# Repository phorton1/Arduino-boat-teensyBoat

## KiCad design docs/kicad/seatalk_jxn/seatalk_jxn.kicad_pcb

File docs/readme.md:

# teensyBoat.ino

**Home** --
**[Electronics](electronics.md)** --
**[3DP](3dp.md)** --
**[Commands](commands.md)**

repos: **[phorton1](https://github.com/phorton1)** --
**teensyBoat Firmware** --
**[teensyBoat App](https://github.com/phorton1/base-apps-teensyBoat/blob/master/docs/readme.md)** --
**[Boat Library](https://github.com/phorton1/Arduino-libraries-Boat/blob/master/docs/readme.md)** --
**[tbESP32 WiFi](https://github.com/phorton1/Arduino-boat-tbESP32/blob/master/docs/readme.md)** --
**[teensyWind Tester](https://github.com/phorton1/Arduino-boat-teensyWind/blob/master/docs/readme.md)** --
**[teensyGPS](https://github.com/phorton1/Arduino-boat-teensyGPS/blob/master/docs/readme.md)**

**teensyBoat.ino** is a Teensy 4.0 firmware and custom PCB that bridges three marine
instrument protocols -- **Seatalk1**, **NMEA 0183**, and **NMEA 2000** -- on a single
compact board.  It is the primary hardware in a three-repo marine electronics system
and the natural entry point for anyone exploring, building, or extending it.  The
firmware includes a complete **virtual boat simulator** and nine **virtual instrument
simulators** that can drive any combination of the three protocols, making it a
self-contained desktop test harness for Raymarine chartplotters and other marine
electronics.  A companion **GP8 connector** on the board drives the analog and pulse
inputs of Raymarine ST50 instruments directly, enabling bench testing of ST50 Speed,
Wind, and Depth instruments without a real boat or real transducers.

## The Three-Repo System

teensyBoat.ino is the hardware hub at the center of a tightly coupled three-repo system:

- **[Arduino-boat-teensyBoat](https://github.com/phorton1/Arduino-boat-teensyBoat)**
  (this repo) -- the Teensy 4.0 firmware and PCB.  Runs standalone as a protocol
  bridge and simulator; exposes a USB serial command interface for monitoring and control.

- **[base-apps-teensyBoat](https://github.com/phorton1/base-apps-teensyBoat)** --
  the companion wxPerl Windows desktop application.  Connects to the firmware over USB
  serial or UDP (via tbESP32) and provides real-time display of boat simulator state,
  live protocol monitoring, and virtual instrument configuration.

- **[Arduino-libraries-Boat](https://github.com/phorton1/Arduino-libraries-Boat)** --
  the shared C++ Arduino library included by the firmware.  Implements the virtual boat
  and instrument simulators, all three protocol stacks, the binary packet framing layer,
  and defines the packet type constants shared with the wxPerl application.

The three repos have independent git histories but are tightly coupled at the
protocol level.  The binary packet type constants defined in the Boat library must
match those in the wxPerl application's `tbBinary.pm`; they are kept in sync manually.

## Binary Serial Protocol

The firmware and wxPerl application communicate over a **binary packet protocol**
carried on the same USB serial port as text output -- or forwarded over UDP by the
**[tbESP32](https://github.com/phorton1/Arduino-boat-tbESP32)** WiFi bridge.
Both the text command interface and the binary telemetry stream are active simultaneously
on a single connection.

Every binary packet begins with a **0x02** start byte (BINARY_FLAG), followed by a
16-bit little-endian payload length and a 16-bit little-endian type code.  Multiple
streams can be active at once; the wxPerl application enables each stream it needs on
connect and disables them on close.

| Packet type         | Value  | Content                                              |
| ------------------- | ------ | ---------------------------------------------------- |
| BINARY_TYPE_PROG    | 0x0001 | Virtual instrument port-mask config and monitor flags |
| BINARY_TYPE_SIM     | 0x0002 | Full boat simulator state (50+ fields, at 1 Hz while running) |
| BINARY_TYPE_ST1     | 0x0010 | Decoded Seatalk1 datagrams from port ST1             |
| BINARY_TYPE_ST2     | 0x0020 | Decoded Seatalk1 datagrams from port ST2             |
| BINARY_TYPE_0183A   | 0x0100 | Raw NMEA 0183 sentences from port A                  |
| BINARY_TYPE_0183B   | 0x0200 | Raw NMEA 0183 sentences from port B                  |
| BINARY_TYPE_2000    | 0x1000 | Decoded NMEA 2000 PGN data                           |

The framing layer is implemented in `boatBinary.cpp` (`startBinary()` / `endBinary()`
in the Boat library) and consumed by the wxPerl application's binary receive loop.

## Hardware

The custom PCB and 3D-printed enclosure design files are included in this repository.

- **[Electronics](electronics.md)** -- KiCad schematics and PCB layouts for the current
  and previous board revisions, Gerber files, and CNC milling gcode for the home-milled
  board1 revision.

- **[3DP](3dp.md)** -- STL and 3MF files for the 3D-printed enclosure, and pre-sliced
  PETG printer gcode.

## Command Interface

The firmware accepts a comprehensive set of **text commands** -- plain
ASCII, case-insensitive, `KEY=VALUE` or `VERB` form, newline-terminated
-- on its USB serial port.  The same commands are forwarded by the
companion **tbESP32** WiFi bridge and by the **teensyBoat.pm** wxPerl
application's HTTP `/api/command` endpoint.

See **[Commands](commands.md)** for the complete reference: virtual boat
control, instrument configuration, protocol monitoring, GP8/ST50 testing,
NMEA 2000 device queries, and binary streaming control.

## Credits

- [**Paul Stoffregen**](https://www.pjrc.com/teensy/) --
  Creator of the Teensy microcontroller platform.  teensyBoat.ino is built
  for the Teensy 4.0.

- [**Thomas Knauf**](http://www.thomasknauf.de/seatalk.htm) --
  *SeaTalk Technical Reference Revision 3.23*.  The primary public reference for
  the Seatalk1 datagram protocol.  The
  **[Arduino Boat Library](https://github.com/phorton1/Arduino-libraries-Boat/blob/master/docs/readme.md)**
  used by this firmware builds on, extends, and in places corrects that work.
  Corrections, extensions, and new datagrams not in Knauf are catalogued on the
  **[Seatalk Knowledge](https://github.com/phorton1/Arduino-libraries-Boat/blob/master/docs/new_st_knowledge.md)**
  page in the Boat Library documentation.

## License

This software is released under the
[**GNU General Public License v3**](../LICENSE.TXT).

## Please Also See

- [**phorton1/base-apps-teensyBoat**](https://github.com/phorton1/base-apps-teensyBoat) --
  The companion wxPerl Windows application.  Monitors and controls the teensyBoat
  firmware over USB serial or WiFi; provides real-time display of simulator state,
  protocol monitoring, and virtual instrument configuration.

- [**phorton1/Arduino-libraries-Boat**](https://github.com/phorton1/Arduino-libraries-Boat) --
  The shared C++ library used by this firmware.  Implements the virtual boat and
  instrument simulators, all three protocol encoders and decoders, and the binary
  packet protocol shared with the wxPerl application.

- [**phorton1/Arduino-boat-teensyGPS**](https://github.com/phorton1/Arduino-boat-teensyGPS) --
  A related device built on the same Boat library: a Teensy/Neo6M GPS that outputs
  Seatalk1 and/or NMEA 2000 for integration into an existing marine instrument network.

- [**phorton1/Arduino-boat-tbESP32**](https://github.com/phorton1/Arduino-boat-tbESP32) --
  The ESP32 WiFi bridge that plugs into teensyBoat's GP8 connector, forwarding the
  USB serial binary protocol over UDP to the wxPerl application over a local network.

- [**phorton1/Arduino-boat-teensyWind**](https://github.com/phorton1/Arduino-boat-teensyWind) --
  A companion device that interfaces directly with a Raymarine ST50/ST60 wind vane
  transducer and outputs Seatalk1 or NMEA 2000.

- [**phorton1/base-apps-raymarine**](https://github.com/phorton1/base-apps-raymarine) --
  Documentation of the reverse-engineered Raymarine SeatalkHS ethernet protocol
  suite.  The teensyBoat hardware was the active instrument platform during that work.

---

**Next:** [Electronics](electronics.md)

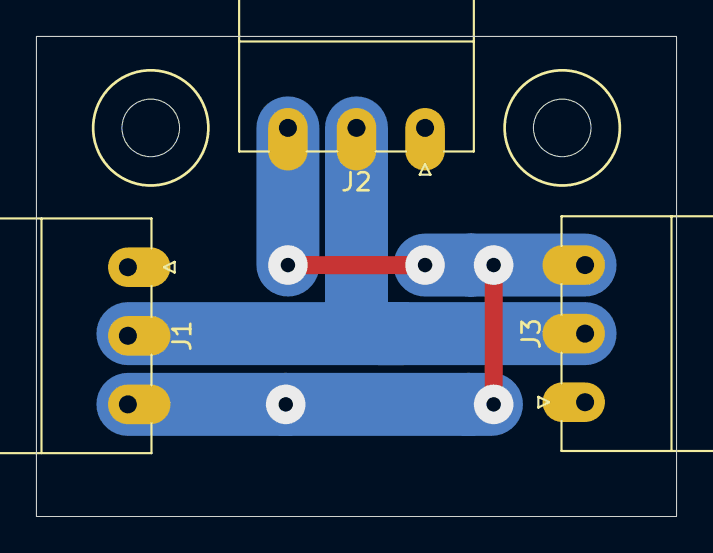
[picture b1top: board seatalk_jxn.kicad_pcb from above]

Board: 2 copper layers, 35.6 x 26.7 mm, 3 parts (0 on the bottom side), 3 nets.

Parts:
J1, J2, J3: Conn_01x03; myPheonix3x3.81_right

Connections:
+12V: J1.2, J2.2, J3.2
DATA: J1.3, J2.3, J3.3
GND: J1.1, J2.1, J3.1

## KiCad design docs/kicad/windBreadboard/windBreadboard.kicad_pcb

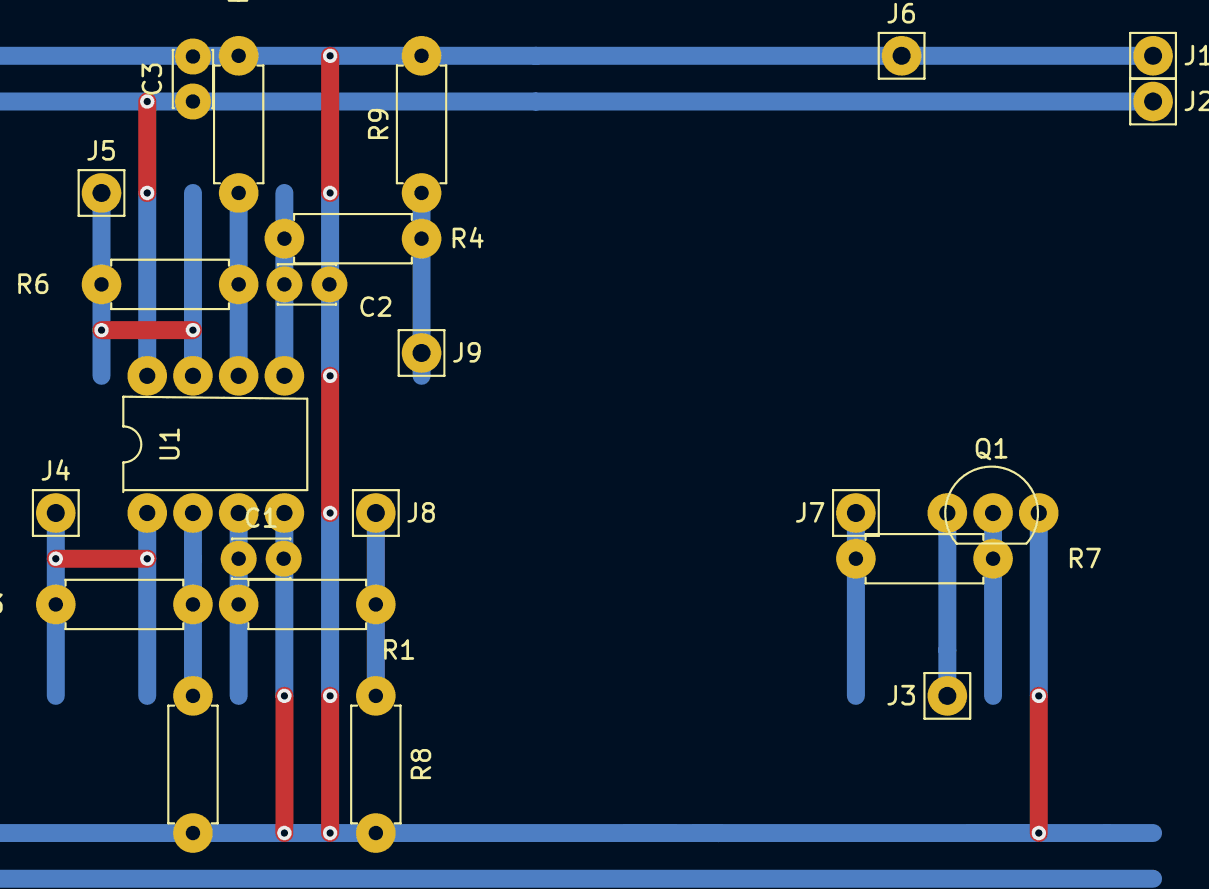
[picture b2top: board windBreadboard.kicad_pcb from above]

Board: 2 copper layers, 23 parts (0 on the bottom side), 13 nets.

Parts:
C1, C2, C3: 100nf; myCapCeramicSmall
J1: ST_GND; myPinHeader_1x01
J2: ST_12V; myPinHeader_1x01
J3: WIND_PULSE_YELLOW; myPinHeader_1x01
J4: SIGNALA_GREEN; myPinHeader_1x01
J5: SIGNALB_BLUE; myPinHeader_1x01
J6: GP8_GND; myPinHeader_1x01
J7: GP8_PULSE_YELLOW; myPinHeader_1x01
J8: GP8_PWMA_GREEN; myPinHeader_1x01
J9: GP8_PWMB_BLUE; myPinHeader_1x01
Q1: BC546; myTransistor
R1, R2, R4, R5, R8, R9: 10K; myResistor
R3, R6: 22K; myResistor
R7: 1K; myResistor
U1: LM358; myDip8

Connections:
+12V: C3.1, J2.1, U1.8
GND: C1.2, C2.2, C3.2, J1.1, J6.1, Q1.3, R2.2, R5.2, R8.2, R9.2, U1.4
unnamed: C1.1, R1.1, U1.3
unnamed: C2.1, R4.1, U1.5
unnamed: Q1.2, R7.1
unnamed: R2.1, R3.2, U1.2
unnamed: R5.1, R6.2, U1.6
PWMA_GREEN: J8.1, R1.2, R8.1
PWMB_BLUE: J9.1, R4.2, R9.1
SIGNALA_GREEN: J4.1, R3.1, U1.1
SIGNALB_BLUE: J5.1, R6.1, U1.7
SPEED_PULSE_YELLOW: J7.1, R7.2
WIND_PULSE_YELLOW: J3.1, Q1.1

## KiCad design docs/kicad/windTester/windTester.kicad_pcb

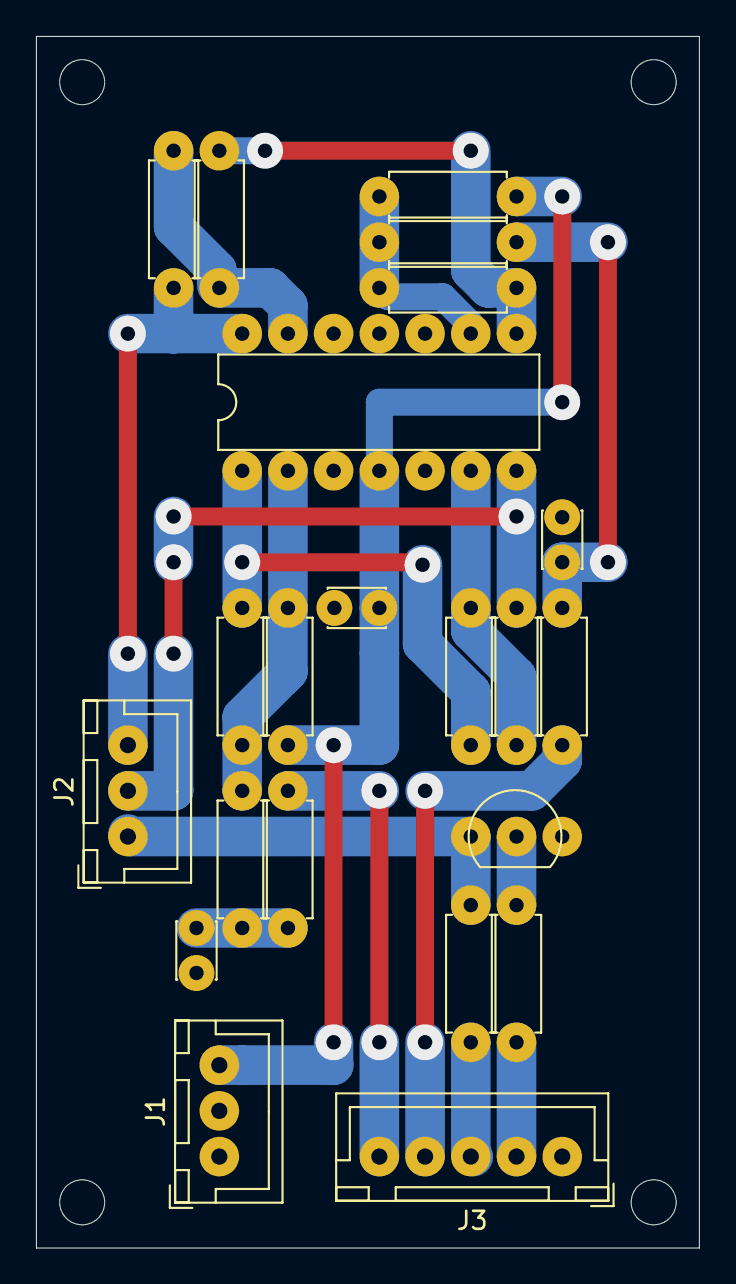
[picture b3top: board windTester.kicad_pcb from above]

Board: 2 copper layers, 36.8 x 67.3 mm, 22 parts (0 on the bottom side), 18 nets.

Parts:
C1, C2, C3: 100nf; myCapCeramicSmall
J1: SEATALK; myJSTx03
J2: INSTRUMENT; myJSTx03
J3: TEENSY_PCB; myJSTx05
Q1: BC547; myTransistor
R1, R2, R5, R6, R7, R8, R11, R12, R14: 10K; myResistor
R3, R9: 68K; myResistor
R4, R10: 12K; myResistor
R13: 1K; myResistor
U1: LM324A; myDip14

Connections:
+5V: J3.3, R14.2
+12V: C3.1, J1.3, R3.1, R9.1, U1.4
GND: C1.2, C2.2, C3.2, J1.1, J3.1, Q1.3, U1.3, U1.5, U1.10, U1.11, U1.12
unnamed: C1.1, R1.1, R2.2
unnamed: C2.1, R7.1, R8.2
unnamed: Q1.2, R13.1
unnamed: R2.1, R3.2, R4.2, U1.2
unnamed: R4.1, R5.2, U1.1
unnamed: R5.1, R6.2, U1.6
unnamed: R10.1, R11.2, U1.8
unnamed: R8.1, R9.2, R10.2, U1.9
unnamed: R11.1, R12.2, U1.13
PWMA: J3.5, R1.2
PWMB: J3.4, R7.2
SIGNALA: J2.2, R6.1, U1.7
SIGNALB: J2.3, R12.1, U1.14
SPEED_SQUARE: J3.2, R13.2
WIND_SQUARE: J2.1, Q1.1, R14.1

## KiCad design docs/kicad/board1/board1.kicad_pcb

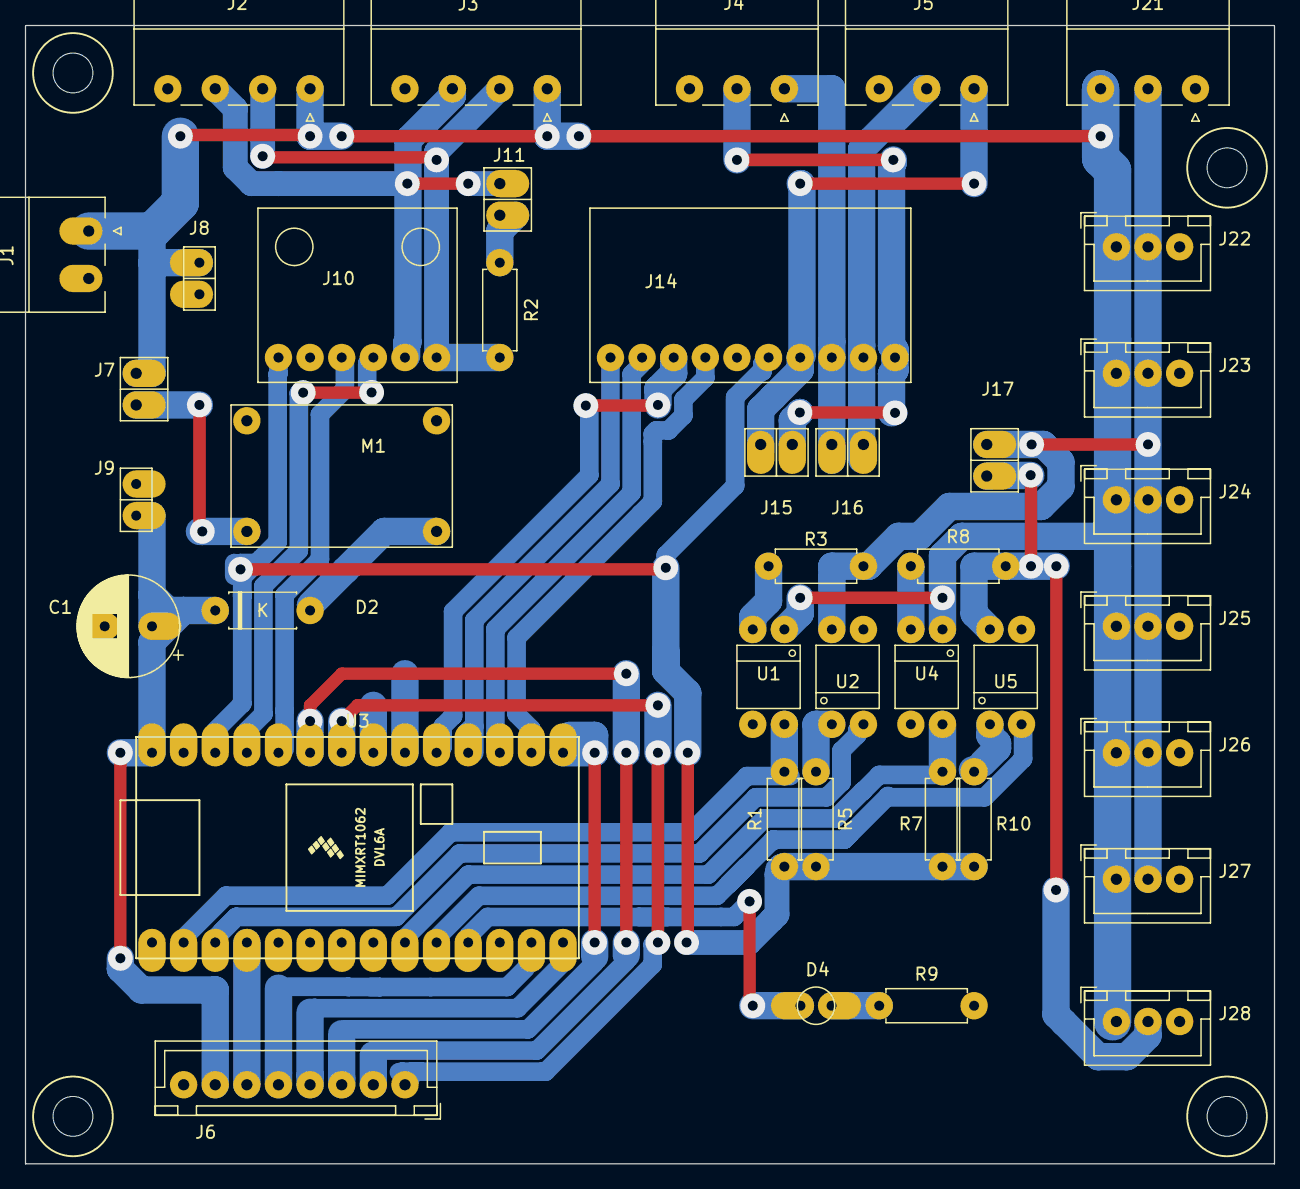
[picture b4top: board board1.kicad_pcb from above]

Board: 2 copper layers, 100.3 x 91.4 mm, 40 parts (0 on the bottom side), 37 nets.

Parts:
C1: 100uf; CP_my100uf
D2: 1N5819; myDiodeSchotsky
D4: ALIVE_LED; led_small_red
J1: INST_POWER; myPheonix2x3.81_right
J2, J3: NMEA2000; myPheonix4x3.81_right
J4: 83A; myPheonix3x3.81_right
J5: 83B; myPheonix3x3.81_right
J6: TEST_RIG; myJSTx08
J7: BUCK_PWR; pinHeader1x2
J8: 12V_TEST; pinSocket1x2
J9: 5V_TEST; pinSocket1x2
J10: SN65HVD230; CANBUS_Module1
J11: CAN_TERMINATOR; pinHeader1x2
J14: MAX3232; MAX3232_Module
J15: AIS; pinHeader1x2
J16: GPS; pinHeader1x2
J17: ST_CONNECTED; pinHeader1x2
J21: ST1; myPheonix3x3.81_right
J22, J23, J24, J25, J26, J27: ST1; myJSTx03
J28: ST2; myJSTx03
M1: BUCK01; myMini360BuckConverter
R1: 10K; myResistor
R2: 120; myResistor
R3, R8: 4.7K; myResistor
R5, R9, R10: 220; myResistor
R7: 10k; myResistor
U1, U2, U4, U5: TLP521; myDip4
U3: myTeensy4.0; teensy40

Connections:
83A_IN: J4.2, J14.10, J15.2
83A_OUT: J4.1, J14.8, J16.1
83B_IN: J5.2, J14.9, J16.2
83B_OUT: J5.1, J14.7, J15.1
+3V3: J10.1, J14.6, R1.1, R5.2, R7.1, R10.2, U3.26
+5V: C1.1, D2.1, J6.7, J9.1, U3.28
+12V: J1.1, J2.1, J3.1, J7.2, J8.1, J21.3, J22.1, J23.1, J24.1, J25.1, J26.1, J27.1, J28.1, U1.1, U4.1
ALIVE_LED: D4.2, U3.11
CANH: J2.3, J3.3, J10.5, J11.2
CANL: J2.2, J3.2, J10.6, R2.1
CRX: J10.3, U3.24
CTX: J10.4, U3.25
GND: C1.2, J1.2, J2.4, J3.4, J4.3, J5.3, J6.8, J8.2, J9.2, J10.2, J14.5, J21.1, J22.3, J23.3, J24.3, J25.3, J26.3, J27.3, J28.3, M1.1, M1.2, R9.2, U1.3, U2.3, U3.1, U3.27, U4.3, U5.3
MISO-UDP_ENABLE: J6.4, U3.14
MOSI-GP: J6.5, U3.13
unnamed: D2.2, M1.3
unnamed: D4.1, R9.1
unnamed: J7.1, M1.4
unnamed: J11.1, R2.2
unnamed: R3.1, U1.2
unnamed: R5.1, U2.1
unnamed: R8.1, U4.2
unnamed: R10.1, U5.1
RX1: R1.2, U1.4, U3.2
RX2: R7.2, U3.9, U4.4
RX3: J14.2, U3.17
RX4: J14.1, U3.18
RX5-T_CS: J6.2, U3.23
SCLK-GP: J6.3, U3.15
SPEED_PULSE-LCD_CS: J6.6, U3.4
ST1: J17.2, J21.2, J22.2, J23.2, J24.2, J25.2, J26.2, J27.2, R3.2, U2.4
ST2: J17.1, J28.2, R8.2, U5.4
TX1: U2.2, U3.3
TX2: U3.10, U5.2
TX3: J14.4, U3.16
TX4: J14.3, U3.19
TX5-LCD_DC: J6.1, U3.22

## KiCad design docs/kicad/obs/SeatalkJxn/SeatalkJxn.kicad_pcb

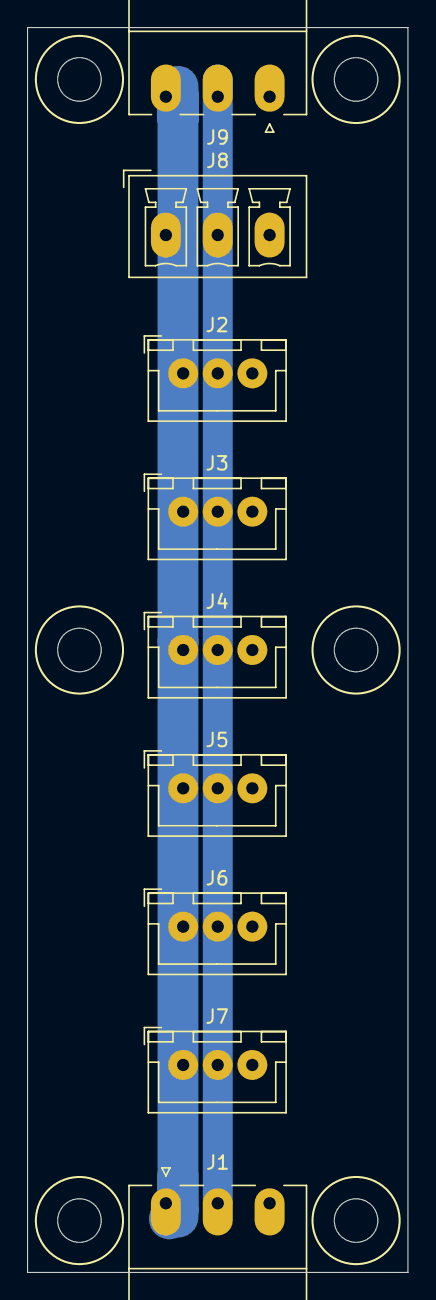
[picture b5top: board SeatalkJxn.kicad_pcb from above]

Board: 2 copper layers, 27.9 x 91.4 mm, 9 parts (0 on the bottom side), 3 nets.

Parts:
J1, J9: Conn_01x03; myPheonix3x3.81_right
J2, J3, J4, J5, J6, J7: Conn_01x03; myJSTx03
J8: Conn_01x03; myPhoenix3x3.81_vertical

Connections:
+12V: J1.1, J2.1, J3.1, J4.1, J5.1, J6.1, J7.1, J8.1, J9.3
GND: J1.3, J2.3, J3.3, J4.3, J5.3, J6.3, J7.3, J8.3, J9.1
data: J1.2, J2.2, J3.2, J4.2, J5.2, J6.2, J7.2, J8.2, J9.2

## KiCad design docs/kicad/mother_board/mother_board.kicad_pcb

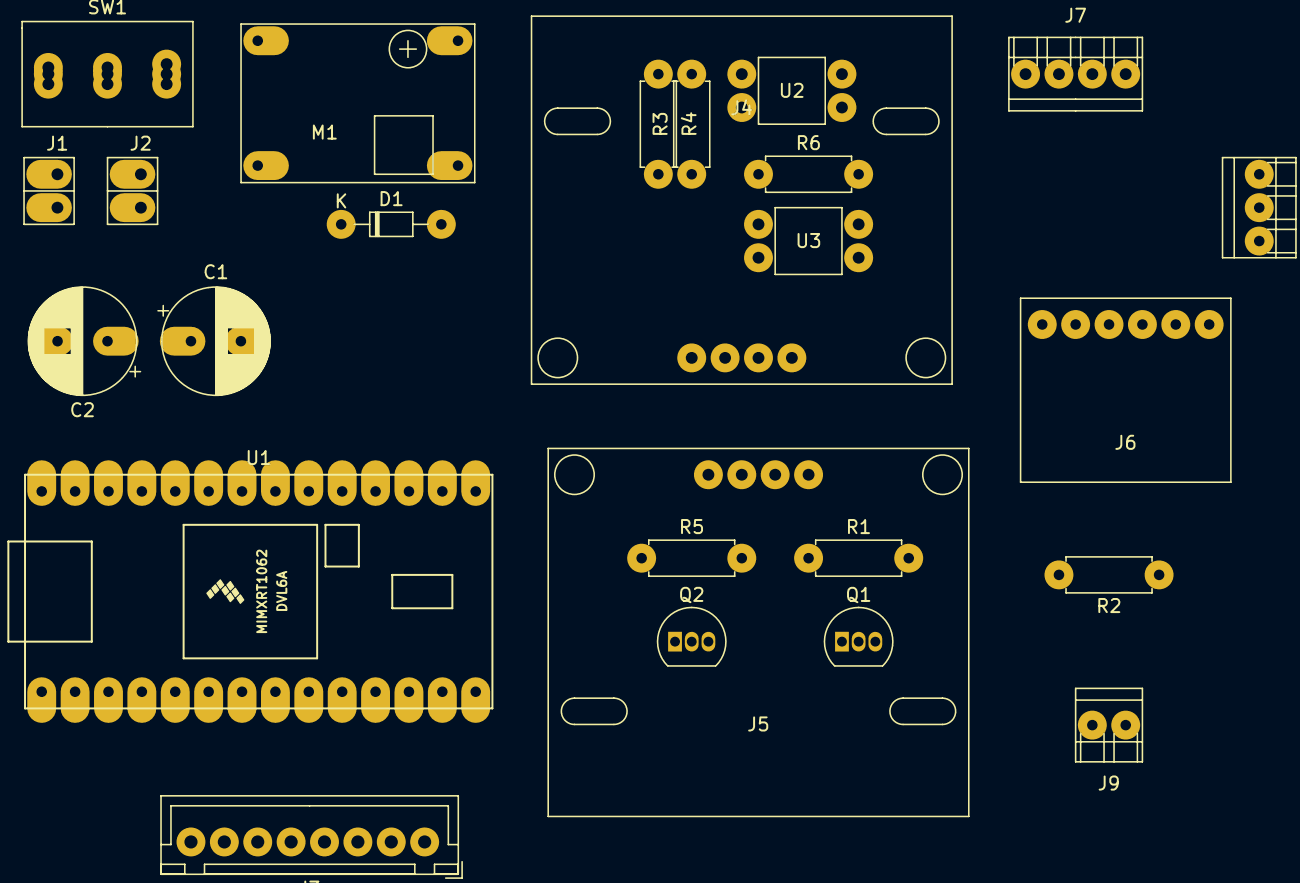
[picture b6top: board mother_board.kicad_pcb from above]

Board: 2 copper layers, 25 parts (0 on the bottom side), 33 nets, no tracks yet.

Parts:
C1, C2: 100uf; CP_my100uf
D1: 1N4003; myZenerDiode
J1: 12V_TEST; pinHeader1x2
J2: 5V_JUMP; pinHeader1x2
J3: TE_DISPLAY; myJSTx08
J4: RS232-1; RS232_Module
J5: RS232-2; RS232_Module
J6: CAN_MODULE; CANBUS_Module1
J7: NMEA200; myTerminalBlock_2.54x04
J8: Seatalk; myTerminalBlock_2.54x03
J9: TEST_ST50; myTerminalBlock_2.54x02
M1: BUCK01; buck-mini360
Q1, Q2: BC547; TO-92_Inline
R1, R5: 100; myResistor
R2, R3: 220; myResistor
R4, R6: 4.7K; myResistor
SW1: ON/OFF; SW_DPDT_BLUE_LEVER
U1: myTeensy4.0; teensy40
U2, U3: TLP521-1; myDip4

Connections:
+3V3: C1.1, J4.1, J5.1, J6.1, R3.2, R4.1, U1.26
+5V: C2.1, J2.2, J3.8, R2.2, U1.28
+12V: J8.3, U2.1
CANH: J6.5, J7.3
CANL: J6.6, J7.2
CAN_12V: J1.2, J7.1, SW1.3
CRX: J6.4, U1.24
CTX: J6.3, U1.25
GND: C1.2, C2.2, J1.1, J3.1, J4.4, J5.4, J6.2, J7.4, J8.1, M1.1, M1.2, Q1.3, Q2.3, U1.27, U2.3, U3.3
LCD_CS: J3.3, U1.12
LCD_DC: J3.4, U1.11
MISO: J3.5, U1.14
MOSI: J3.2, U1.13
unnamed: D1.1, J2.1
unnamed: D1.2, M1.3
unnamed: J8.2, R6.2, U3.4
unnamed: M1.4, SW1.2
unnamed: Q1.2, R1.1
unnamed: Q2.2, R5.1
unnamed: R3.1, U3.1
unnamed: R6.1, U2.2
RX2: R4.2, U1.9, U2.4
RX3: J4.2, U1.17
RX4: J5.2, U1.18
SCLK: J3.6, U1.15
SPEED_PULSE: R5.2, U1.6
ST50_LOG_GREEN: J9.1, Q2.1
ST50_WIND_YELLOW: J9.2, Q1.1, R2.1
TX2: U1.10, U3.2
TX3: J4.3, U1.16
TX4: J5.3, U1.19
T_CS: J3.7, U1.5
WIND_PULSE: R1.2, U1.7

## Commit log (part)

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2025-08-28 initial commit - direct port of NMEA_SENSOR project using teensy 4.0 and SN65HVD230 module
2025-08-28 initial design and implementation of instSimularor, a layer above the boatSimulator that knows about NMEA2000, NMEA0183, and Seatalk protocols
2025-09-01 build max3232_board - doesnt work - see comments and TEST_IT which outputs slow square wave
2025-09-01 added teensyBoat/readme.md; slight cleanup to Arduino-libraries-boat/instSimulator.h too
2025-09-01 started teensyBoat mother_board; gave one more try to max3232_board - no joy
2025-09-08 cleaned up teensyBoat implementation a bit by re-organizing /Arduino/libraries/boat
2025-09-08 created initial intetgrated teensyBoat PCB (docs/kicad/initial_board)
2025-09-11 cleanup
2025-09-11 INITIAL COMBINED BREADBOARD supporting all three protocols - added instXXX_in, out, and h files as needed - flesh out protocols a bit - implemented command processor, - implement rudimentary text mon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
2025-09-14 teensyBoat (perl, ino, and library) first working BINARY_PROTOCOL
2025-09-14 added tbListCtrl.pm for showing ST changes; added ST_SAT_INFO decoding and some 0183 satellite output
2025-09-17 sanity checkin after getting partial success sending NMEA0183 to RNS
2025-09-18 change teensyBoat startup defaults; get rid of obs text file
2025-09-19 change default instruments
2025-09-21 added winProg to Perl app and support in INO and instSimularor. Fixed some bugs in tbListCtrl
2025-10-21 added water current simulation (heading, water_speed, current_angle, current_speed) and calculateOverGround for cog and sog - added calculateOverGround - pain in the ass reworking calculateApparentWi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
2025-10-22 add Pub::WX::Frame::setHowRestore and $ini_file; clean up window::new() calls; clean up uses; add / clean up $dbg constants
2025-10-23 teensyBoat: - winBoat - added new fields - winST - separate sends from receives Simulator: - Turning Routing off no longer turns Autopilot off - add & utilitize XTE and TRIP/TOTAL simulation - cleanu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
2025-11-04 improved NMEA2000 and ST messages - added generic headingTo and distanceTo methods to boatSimulator.h - added and advertise more organized PGNS in inst2000 - added date/time xmit to ST gps instrument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
2025-11-06 switched breadboard to orange MAX3232 boards; prep for testing two NMEA0183 ports
2025-11-08 added 2nd NMEA0183 port (red MAX3232 board) with FWD and UI; simplified Monitoring scheme with UI - redesigned breadboard - tested VHF -> E80 with forwarding and without breadboard - consistent monit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
2025-11-08 got 2nd (now 1st) Seatalk working on breadboard RX1; Seatalk2 to become RX2
2025-11-09 Added 2nd Seatalk port named PORT_ST1 and PORT_ST2, with forwarding and UI support changed binary type BINARY_TYPE_ST1 and added BINARY_TYPE_ST2 monitoring/winST shows: <-- STx_NAME for messages rece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
2025-11-10 cleaned up INO Help messages and command implementations added several new decoded ST Log/Speed messages implemented ST50 speed pulses added LAMP=x ST instrument specific command; figured out E80/GX2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
2025-11-10 designed new board0 using relays for passive/active control and lots of features
2025-11-16 added new teensyBoat PCB (with MAX3333 and better footprints) kicad projects board0 (using relays) and board0_max33333 (using IC analog switch)
2025-11-19 create actual boat teensyBoat pcb board1; move other kicad stuff to _obs; add/fix kicad footprints
2025-11-24 implement ALIVE_LED=9 on breadboard
2025-11-24 fix incorrect CRX/CTX routing
2025-11-24 fix build dir
2025-11-24 added experimental tbESP32 serial<->UDP teensyBoat.ino myIOT forwarding device
2025-11-24 renamed 8 pin connector net names in accordance with comments
2025-11-24 added global udp_enable for SERIAL_ESP32 turned on by PIN_UDP_ENABLE in instSimulator.cp - improved 8 pin connector comments - only output UDP packets if both SERIAL_ESP32 is defined and PIN_UDP_ENAB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
2026-01-05 reworked existing teensyBoat PCB for tbESP32 connector - ran Serial5 (RX5 & TX5) to 8 pin connector - updated schematic and PCB with comments - changed PIN_UDP_ENABLE from 4 to 12 (mosi)
2026-01-06 teensyBoat multi-repo change in prep for ACTUAL BOAT monitoring - rename boat->boat_sim - rename instruments->inst_sim - rename "boat" window to "Boat Sim" - rename BINARY_TYPE_BOAT -> BINARY_TYPE_SI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
2026-01-08 created 2nd teensyBoat PCB then modified Pheonix connector pads and deleted plot/gcode
2026-01-08 3D Print prelimnary teensyBoatMount1
2026-01-09 3D print 2nd teensyBoat box
2026-01-13 latest teensyBoat changes from apartment
2026-01-14 Added B_XXX binary mode commands and optimized tb INO and PM to only turn on binary packets when needed by specific windows
2026-01-17 reworked Pulse UI and implementation to test HH oscilloscope and provide for more flexibility in the future
2026-01-21 Turn off speed pulse for checkin
2026-01-23 Implemented General Purpose Connector (GP8) modes: OFF,PULSE,ESP32,NEO6M, with UI, save to EPROM, etc - Features turned on or off at runtime - Code can be eliminated with #defines - Protects pinouts 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
2026-01-26 fix typo
2026-02-03 added LICENSE.txt
2026-02-03 reworked neoGPS to be callable from new teensyGPS.ino program - renamed neo6M_GPS.cpp to neoGPS.cpp - added neoGPS.h - modified teensyBoat UI and instSimulator to support NEOST and NEO2000 "GP8" mode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
2026-02-06 remove UI/implementation and move neoGPS to teensyGPS repo - cleanup NMEA2000 device (teensyBoat vs teensyGPS) initialization - update preferences.txt's to back two plugs on Lenovo3
2026-02-11 checkin kicad design for theoretical PWM/opAmp based ST50 Wind Instrument tester
2026-02-11 expanded G_MON values to uint32_t's per port with associated binary and UI changes added NMEA2000 Self and Raw instrument monitoring
2026-02-12 changed pulseHz to a float for sub 1 hz testing
2026-02-12 played around again with idea of a windTester opAmp driven breadboard
2026-02-13 Panic Checking - windTester PCB right after coPilot tells me it wont generate 2-8V preceding new design
2026-02-14 didn't mill. Changed to LM358 dip8 and windBreadboard for testing ST50 Wind & Speed
2026-02-14 ST50 WIND DAY - Added GP8 "Wind Mode", cleanup of GP8 and test_mode, including implemented raw PWM and non-working Simulated WindAngle to PWM math - fixed a lot of comments, made members out of instS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
2026-02-16 SANITY CHECKIN of ST50 windTester breadboard notes, observations, conclusions, and working-ish code
2026-02-17 rework GP8 ST Testing modes APIs - add WIND_CIRCLE ui for explicit calibration/measurement of ST50 Wind Instrument windTester cycle
2026-02-20 rework teensyGPS incluging new pins, refactoring it and teensyBoat ST stuff, NMEA2000 init, and monitoring commands
2026-04-03 add gcode .gitignores to project docs 3dp folders
2026-04-23 Added http tooling for CLAUDE to be able to see/run teensyBoat
2026-04-24 updated teensyBoat documentation chain
2026-05-10 teensyBoat documentation pass
2026-05-10 add teensyBoat simulator water temperature; output in instST_out::logInst(), verified it comes back in tracks on the E80. Added WT=command to teensyBoat.ino and display in wx winBoatSim
2026-05-11 added Boat Library: new_st_knowledge.md and links from teensyBoat.ino and main Boat library readme's
2026-05-16 rework all teensyBoat repos documentation particularly with regards to command tables and the boat driving guide(s)
2026-05-18 initial realboat design foray
